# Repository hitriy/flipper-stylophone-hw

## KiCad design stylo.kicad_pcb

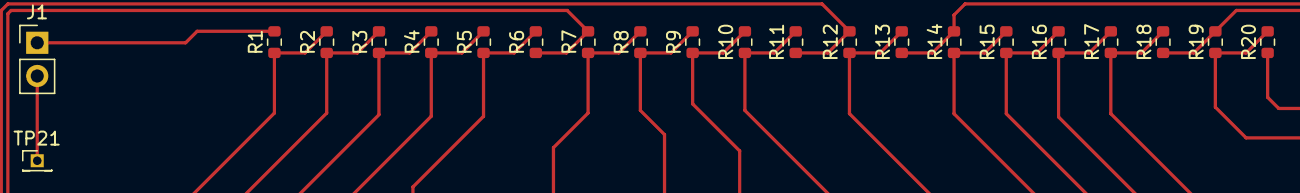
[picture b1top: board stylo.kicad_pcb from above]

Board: 2 copper layers, 22 parts (0 on the bottom side), 21 nets.

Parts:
J1: Conn_01x02; PinHeader_1x02_P2.54mm_Vertical
R1, R2, R3, R4, R5, R6, R7, R8, R9, R10, R11, R12, R13, R14, R15, R16, R17, R18, R19, R20: R; R_0603_1608Metric
TP21: Stylo; PinHeader_1x01_P1.27mm_Vertical

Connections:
unnamed: J1.1, R1.2
unnamed: R1.1, R2.2
unnamed: R2.1, R3.2
unnamed: R3.1, R4.2
unnamed: R4.1, R5.2
unnamed: R5.1, R6.2
unnamed: R6.1, R7.2
unnamed: R7.1, R8.2
unnamed: R8.1, R9.2
unnamed: R9.1, R10.2
unnamed: R10.1, R11.2
unnamed: R11.1, R12.2
unnamed: R12.1, R13.2
unnamed: R13.1, R14.2
unnamed: R14.1, R15.2
unnamed: R15.1, R16.2
unnamed: R16.1, R17.2
unnamed: R17.1, R18.2
unnamed: R18.1, R19.2
unnamed: R19.1, R20.2
unnamed: J1.2, TP21.1
